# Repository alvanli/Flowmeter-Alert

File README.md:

FILES:  
/NRF/Photoresistor for transmitter/detector code  
/NRF/Testing/LCD/lcd_keypad_shield for receiver/LCD code

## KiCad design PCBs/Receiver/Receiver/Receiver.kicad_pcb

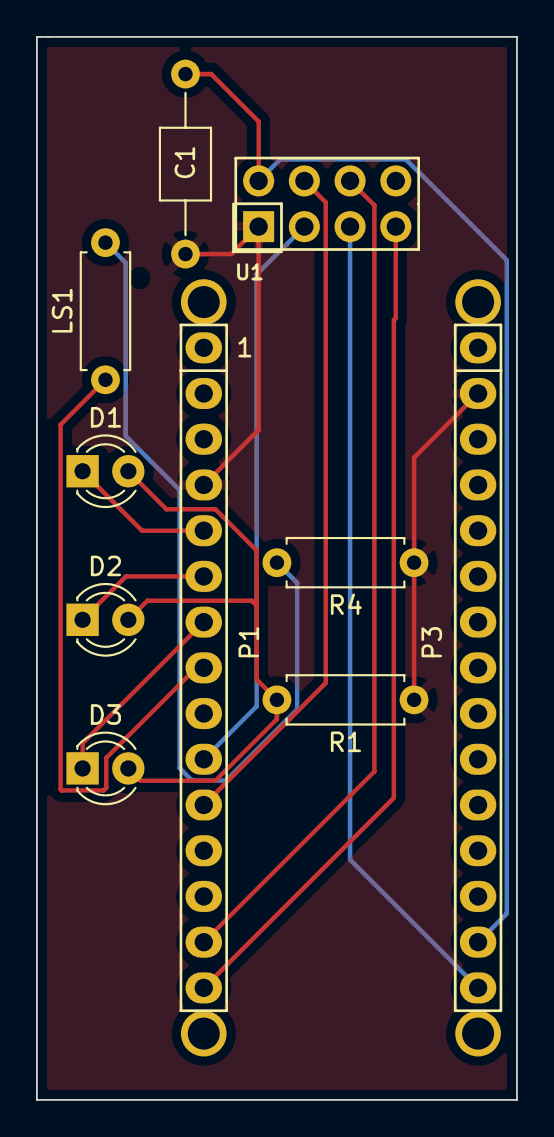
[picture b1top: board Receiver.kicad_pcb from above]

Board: 2 copper layers, 26.7 x 59.1 mm, 14 parts (0 on the bottom side), 14 nets.

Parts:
C1: C; C_Axial_L3.8mm_D2.6mm_P10.00mm_Horizontal
D1, D2, D3: LED; LED_D3.0mm
LS1: Speaker; R_Axial_DIN0207_L6.3mm_D2.5mm_P7.62mm_Horizontal
P1: Digital; Socket_Strip_Arduino_1x15
P3: Analog; Socket_Strip_Arduino_1x15
P3#2, P4, P5, P6: CONN_01X01; 1pin_Nano
R1, R4: R; R_Axial_DIN0207_L6.3mm_D2.5mm_P7.62mm_Horizontal
U1: NRF24L01_Breakout; NRF24L01

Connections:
+3V3: C1.2, P3.14, U1.2
/2: D1.1, P1.5
/3(**): D2.1, P1.6
/4: D3.1, P1.7
/5(**): LS1.1, P1.8
/7: P1.10, U1.3
/8: P1.11, U1.4
/11(**/MOSI): P1.14, U1.6
/12(MISO): P1.15, U1.7
/13(SCK): P3.15, U1.5
/Reset: P1.3, P3.3
GND: C1.1, P1.4, P3.2, R1.1, R4.1, U1.1
unnamed: D1.2, D2.2, D3.2, R1.2
unnamed: LS1.2, R4.2

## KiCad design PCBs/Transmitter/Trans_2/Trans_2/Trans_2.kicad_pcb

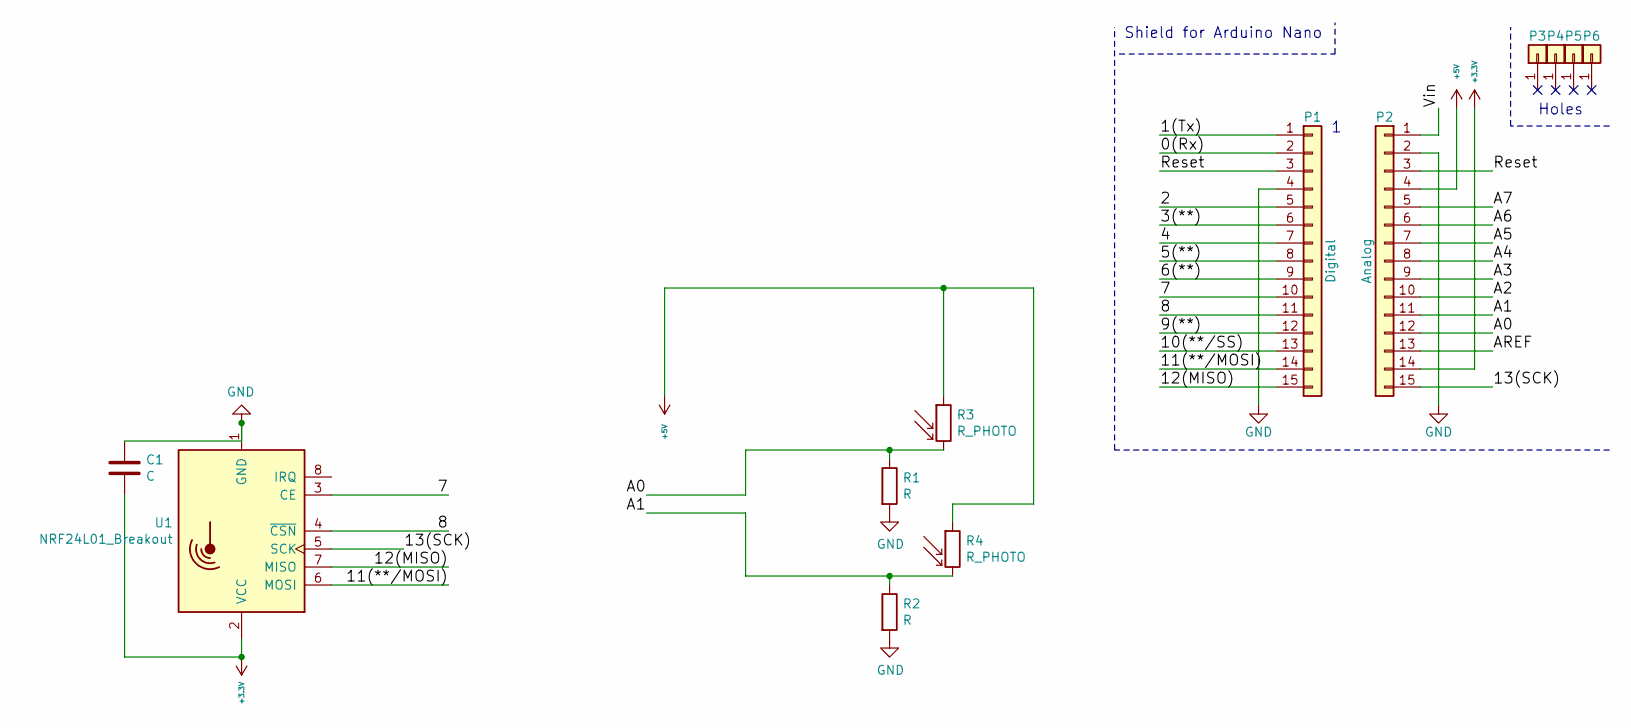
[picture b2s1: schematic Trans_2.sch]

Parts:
C1: C; C_Axial_L3.8mm_D2.6mm_P10.00mm_Horizontal
P1: Digital; Socket_Strip_Arduino_1x15
P2: Analog; Socket_Strip_Arduino_1x15
P3, P4, P5, P6: CONN_01X01; 1pin_Nano
R1, R2: R; R_Axial_DIN0204_L3.6mm_D1.6mm_P7.62mm_Horizontal
R3: R_PHOTO; R_Axial_DIN0204_L3.6mm_D1.6mm_P7.62mm_Horizontal
R4: R_PHOTO; R_Axial_DIN0204_L3.6mm_D1.6mm_P5.08mm_Vertical
U1: NRF24L01_Breakout; nRF24L01_Breakout

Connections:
+3V3: C1.2, P2.14, U1.2 (VCC)
+5V: P2.4, R3.1, R4.1
/0(Rx): P1.2
/1(Tx): P1.1
/2: P1.5
/3(**): P1.6
/4: P1.7
/5(**): P1.8
/6(**): P1.9
/7: P1.10, U1.3 (CE)
/8: P1.11, U1.4 (~CSN)
/9(**): P1.12
/10(**/SS): P1.13
/11(**/MOSI): P1.14, U1.6 (MOSI)
/12(MISO): P1.15, U1.7 (MISO)
/13(SCK): P2.15, U1.5 (SCK)
/A0: P2.12, R1.1, R3.2
/A1: P2.11, R2.1, R4.2
/A2: P2.10
/A3: P2.9
/A4: P2.8
/A5: P2.7
/A6: P2.6
/A7: P2.5
/AREF: P2.13
/Reset: P1.3, P2.3
/Vin: P2.1
GND: C1.1, P1.4, P2.2, R1.2, R2.2, U1.1 (GND)

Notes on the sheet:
Holes
Shield for Arduino Nano

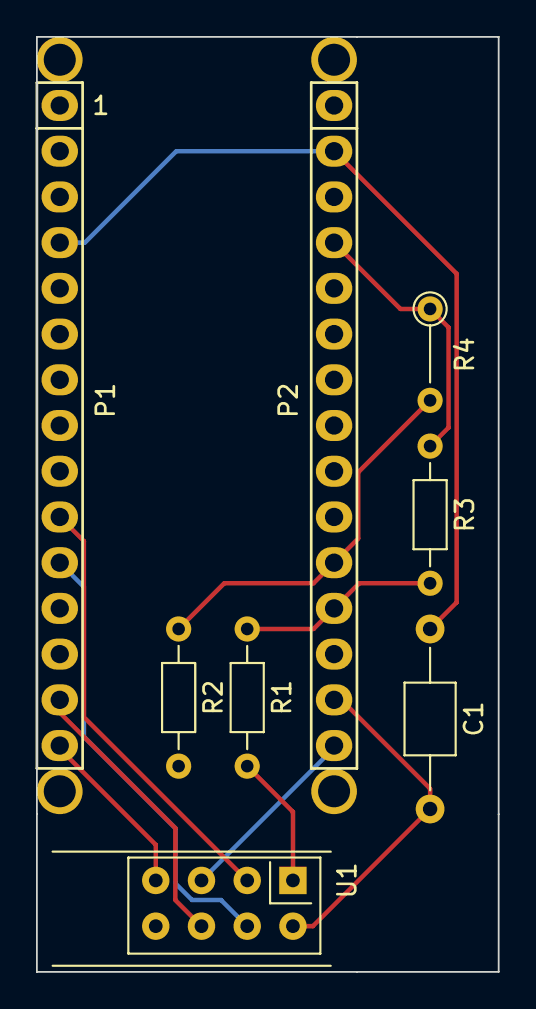
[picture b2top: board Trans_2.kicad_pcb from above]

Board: 2 copper layers, 25.7 x 51.9 mm, 12 parts (0 on the bottom side), 11 nets.

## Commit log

2021-07-02 add parts
2021-07-02 added some nrf code (not working)
2021-07-02 reorg
2021-07-02 added receiver and transmitter code
2021-07-06 added pcb for transmitter
2021-07-06 added receiver pcb
2021-07-07 added lcd sample code and schematic
2021-07-07 holder cad
2021-07-08 added laser rig and modified holdder
2021-07-08 added pillboi versions
2021-07-08 modified pillboi rigs
2021-07-09 shrank ball
2021-07-09 wireless stuff
2021-07-09 added transmitter code to photoresistor
2021-07-09 update pin numbers
2021-07-09 add button code
2021-07-09 radio
2021-07-09 add separate variables for curr1 and curr2
2021-07-10 updated keypad shield keys
2021-07-11 functional UI draft
2021-07-12 Moved files
2021-07-12 refactor
2021-07-12 changed light level calibration
2021-07-12 print thresholds
2021-07-12 oops
2021-07-12 added bright and dim cycles
2021-07-12 minor photores code changes
2021-07-12 test laser
2021-07-12 minor changes
2021-07-12 added alarm code
2021-07-12 beginning of get ball location
2021-07-12 add base joystick code
2021-07-12 If statements for the location of the ball
    ball blocks laser:
    light down
    resistor up
    above threshold
    return 1
2021-07-12 updated schematic for receiver and transmitter
2021-07-12 test
2021-07-12 fix button/joystick logic
2021-07-12 some stuff
2021-07-12 fix logic
2021-07-12 finish menu selection
2021-07-12 add back button
2021-07-12 refactored ball location signal; transmitter sends condensed message
2021-07-12 Revert "refactored ball location signal; transmitter sends condensed message"
    This reverts commit c0851e05014274608f68900df9973a4124388c2b.
2021-07-12 merged lcd and receiver
2021-07-14 replaced delay function
2021-07-14 replace delay
2021-07-17 folder reorg
2021-07-17 maybe fix for alarm no delay
2021-07-17 added test files for receiver and transmitter
2021-07-17 reorganized repo
2021-07-17 rearragned dir
2021-07-18 migrate alarm code to header
2021-07-18 moved lcd to header
2021-07-18 modified lcd change files to work
2021-07-18 nothing much
2021-07-18 transmitter modularize
2021-07-18 make calib return int instead of void
2021-07-20 led and buzzer
2021-07-20 changed pins
2021-07-21 force refresh after msg update and moved logic to transmitter
2021-07-21 more transmissions
2021-07-21 add flash to alarm sequence
2021-07-21 send all the time
2021-07-21 fix receiver and transmitter code according to testing
2021-07-22 updated receiver case
2021-07-22 changed gitignore
2021-07-22 done tasks 2, 3, 4
2021-07-22 top v2
2021-07-22 Bottom casing v1
2021-07-22 Added 0.5mm to laser rig hole size
2021-07-22 attachments
2021-07-22 added casing top to mock ass
2021-07-22 added basket to agss holder and casing bottom to assembly
2021-07-23 Modified dims of receiver case
2021-07-23 modified casing
2021-07-23 debugging 1
2021-07-23 fixing flash
2021-07-23 changed threshold related menu items
2021-07-23 added data
2021-07-24 user testing pt. 1
2021-07-24 user testing pt. 2
2021-07-24 fix for prev
2021-07-24 renamed directory
2021-07-24 renamed dirs
2021-07-25 added vghigh
2021-07-25 added data for response time
2021-07-25 edited schematic
2021-07-27 added analysis
2021-07-27 modified analysis py
2021-07-27 updated scatter plot
